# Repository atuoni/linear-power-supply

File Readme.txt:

These files are a Linear Power Supply from 0 to 24v of output and adjustable current. 
I considered an output limit current of 500mA in this circuit.

I added the gerbers files of PCB. The files were made in Kicad software.
The .pdf files are the schematic and pcb layout.

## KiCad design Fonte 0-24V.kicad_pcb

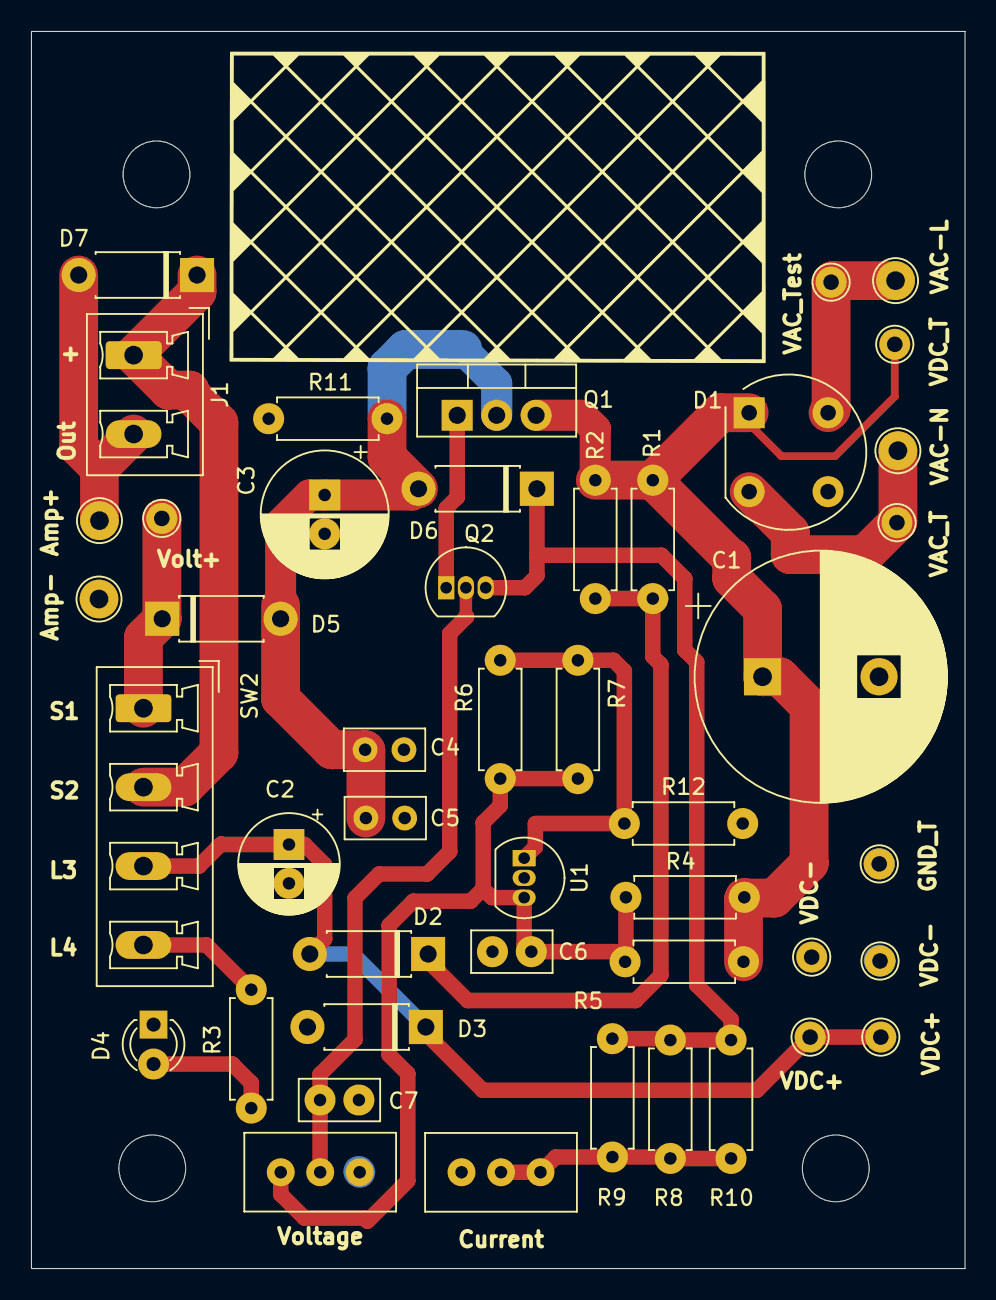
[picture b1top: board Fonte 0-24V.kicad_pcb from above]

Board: 2 copper layers, 60.1 x 79.6 mm, 46 parts (0 on the bottom side), 18 nets.

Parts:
C1: 2200uF x 50V; CP_Radial_D16.0mm_P7.50mm
C2: 100uFx25v; CP_Radial_D6.3mm_P2.50mm
C3: 100uF/50v; CP_Radial_D8.0mm_P2.50mm
C4: 100nF; C_Disc_D5.0mm_W2.5mm_P2.50mm
C5: 100pF; C_Disc_D5.0mm_W2.5mm_P2.50mm
C6, C7: 10nF; C_Disc_D5.0mm_W2.5mm_P2.50mm
D1: W02G; Diode_Bridge_Round_D9.8mm
D2, D3: 12v; D_DO-41_SOD81_P7.62mm_Horizontal
D4: LED_ON; LED_D3.0mm
D5: 1N5819; D_DO-41_SOD81_P7.62mm_Horizontal
D6, D7: 1N4007; D_DO-41_SOD81_P7.62mm_Horizontal
J1: Output; PhoenixContact_MCV_1,5_2-G-5.08_1x02_P5.08mm_Vertical
Q1: TIP32C; TO-220-3_Vertical
Q2: BC337; TO-92_Inline
R1, R2, R3, R4: 2k2; R_Axial_DIN0207_L6.3mm_D2.5mm_P7.62mm_Horizontal
R5, R8, R9, R11, R12: 10k; R_Axial_DIN0207_L6.3mm_D2.5mm_P7.62mm_Horizontal
R6, R7: 200k; R_Axial_DIN0207_L6.3mm_D2.5mm_P7.62mm_Horizontal
R10: 10k*; R_Axial_DIN0207_L6.3mm_D2.5mm_P7.62mm_Horizontal
RV2: 50k; Potentiometer_Bourns_3296W_Vertical
RV3: 1M; Potentiometer_Bourns_3296W_Vertical
SW2: SW_ON_OFF; PhoenixContact_MCV_1,5_4-G-5.08_1x04_P5.08mm_Vertical
TP1: VDC_Test; TestPoint_THTPad_D2.0mm_Drill1.0mm
TP2: VAC-P_Test; TestPoint_THTPad_D2.0mm_Drill1.0mm
TP3: VAC-P; TestPoint_THTPad_D2.5mm_Drill1.2mm
TP4: VAC-N; TestPoint_THTPad_D2.5mm_Drill1.2mm
TP5, TP6: VDC+; TestPoint_THTPad_D2.0mm_Drill1.0mm
TP7: VAC-N_Test; TestPoint_THTPad_D2.0mm_Drill1.0mm
TP8, TP9: VDC-; TestPoint_THTPad_D2.0mm_Drill1.0mm
TP10: GND_Test; TestPoint_THTPad_D2.0mm_Drill1.0mm
TP11: Volt+; TestPoint_THTPad_D2.0mm_Drill1.0mm
TP12: Amp-; TestPoint_THTPad_D2.5mm_Drill1.2mm
TP13: Amp+; TestPoint_THTPad_D2.5mm_Drill1.2mm
U1: TL431LP; TO-92_Inline

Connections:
24VAC-F: D1.4, TP2.1, TP3.1
24VAC-N: D1.2, TP4.1, TP7.1
32VDC: C1.1, D1.1 (+), Q1.3 (E), R1.2, R2.2, R4.1, R5.1, TP1.1
/SW+: C2.1, D2.2 (A), D3.1 (K), SW2.3, TP5.1, TP6.1
/SW_Led: R3.1, SW2.4
GND: C1.2, C2.2, C3.2, C4.2, C5.2, C6.2, C7.2, D1.3 (-), D3.2 (A), D4.1 (K), R11.2, R12.2, RV2.3, RV3.3, TP8.1, TP9.1, TP10.1, TP12.1, U1.2 (A)
unnamed: D2.1 (K), R1.1, R2.1
unnamed: D4.2 (A), R3.2
unnamed: C3.1, C4.1, C5.1, D5.2 (A), D6.2 (A), Q1.2 (C), R11.1
unnamed: D5.1 (K), SW2.1, TP11.1
unnamed: D6.1 (K), Q2.3 (E), R8.1, R9.1, R10.1
unnamed: D7.2 (A), J1.2, TP13.1
unnamed: D7.1 (K), J1.1, SW2.2
unnamed: Q1.1 (B), Q2.1 (C)
unnamed: C7.1, Q2.2 (B), RV2.2
unnamed: R8.2, R9.2, R10.2, RV3.1, RV3.2
unnamed: C6.1, R4.2, R5.2, R6.1, R7.1, RV2.1, U1.3 (K)
unnamed: R6.2, R7.2, R12.1, U1.1 (REF)

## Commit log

2024-02-03 version 1.0
